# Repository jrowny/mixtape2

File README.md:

# A PCB for my mixtape project

_NOTE:_ this revision has NOT been tested! I changed some things from the video including moving the encoderes to different GPIOs and fixing the microsd card. Please verify closely before ordering.

3D models here: https://makerworld.com/en/models/3335806-cassette-mixtape-mp3-player-2-0#profileId-3789001
Video here: https://youtu.be/otXrFBq0HWQ

## This project was sponsored by NextPCB

Get your first PCB order for $0.1 via NextPCB: https://www.nextpcb.com/?code=JonathanRowny
Build PCBA in days with fully automated assembly: https://www.nextpcb.com/rev0-pcb

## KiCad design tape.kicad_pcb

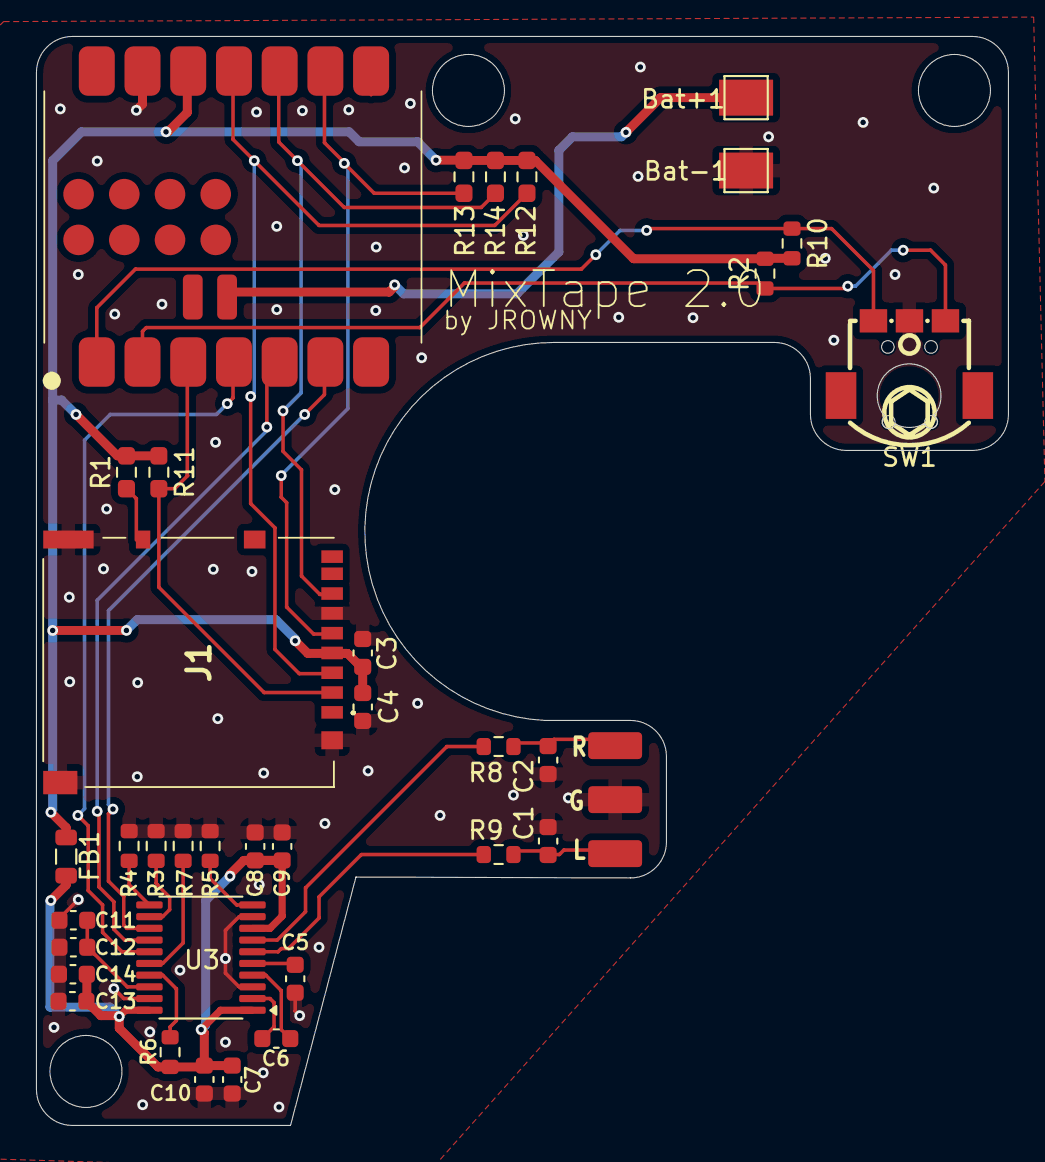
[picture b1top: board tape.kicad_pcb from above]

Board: 2 copper layers, 54.0 x 60.5 mm, 36 parts (0 on the bottom side), 26 nets.

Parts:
Bat+1: Bat+; TestPoint_Pad_2.0x2.0mm
Bat-1: Bat-; TestPoint_Pad_2.0x2.0mm
C1, C2: 2.2nF; C_0603_1608Metric
C3, C7, C9, C11, C14: 10uf; C_0603_1608Metric
C4, C8, C10, C12, C13: 0.1uF; C_0603_1608Metric
C5, C6: 2.2uF; C_0603_1608Metric
FB1: FerriteBead_Small; L_0805_2012Metric
J1: Micro_SD_Card_Det_Hirose_DM3AT; DM3ATSFPEJM5
R1, R11, R12, R13, R14: 10k; R_0603_1608Metric_Pad0.98x0.95mm_HandSolder
R2, R3, R4, R5, R6, R7, R10: 10k; R_0603_1608Metric
R8, R9: 470; R_0603_1608Metric
SW1: RotaryEncoder; EC05E1220401-JRmoded
U1: XIAO-ESP32-S3-SMD; XIAO-ESP32S3-SMD
U2: audio_out
U3: PCM5102A; TSSOP-20_4.4x6.5mm_P0.65mm

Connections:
/3v3: C3.2, C4.2, FB1.1, J1.4 (VDD), R1.1, R2.2, R10.2, R11.1, R12.1, R13.1, R14.1, U1.12 (3V3)
/3v3f: C7.1, C8.1, C9.1, C10.1, C13.1, C14.2, FB1.2, R6.2, U3.1 (CPVDD), U3.8 (AVDD), U3.20 (DVDD)
/BAT: Bat+1.1 (1_1), U1.15 (BAT)
/ENC_A: R2.1, SW1.A, U1.2 (GPIO2_A1_D1)
/ENC_B: R10.1, SW1.B, U1.1 (GPIO1_A0_D0)
/I2S_BCLK: U1.6 (GPIO6_A5_D5_SCL), U3.13 (BCK)
/I2S_DATA: U1.5 (GPIO5_A4_D4_SDA), U3.14 (DIN)
/I2S_LRC: U1.4 (GPIO4_A3_D3), U3.15 (LRCK)
/LDOO: C11.2, C12.1, U3.18 (LDOO)
/OUT_L: C1.2, R9.1, U2.1 (audio_left)
/OUT_R: C2.1, R8.1, U2.3 (audio_right)
/SD_CS: J1.2 (DAT3/CD), R11.2, U1.3 (GPIO3_A2_D2)
/SPI_MISO: J1.7 (DAT0), R14.2, U1.10 (GPIO8_A9_D9_MISO)
/SPI_MOSI: J1.3 (CMD), R12.2, U1.11 (GPIO9_A10_D10_MOSI)
/SPI_SCK: J1.5 (CLK), R13.2, U1.9 (GPIO7_A8_D8_SCK)
GND: Bat-1.1 (1_1), C1.1, C2.2, C3.1, C4.1, C5.2, C7.2, C8.2, C9.2, C10.2, C11.1, C12.2, C13.2, C14.1, J1.6 (VSS), R3.1, R4.1, R5.1, R7.1, SW1.C, U1.13 (GND), U1.16 (GND), U2.2 (gnd), U3.3 (CPGND), U3.9 (AGND), U3.19 (DGND)
unnamed: C6.2, U3.4 (CAPM)
unnamed: C6.1, U3.2 (CAPP)
unnamed: R5.2, U3.10 (DEMP)
unnamed: R4.2, U3.11 (FLT)
unnamed: R7.2, U3.16 (FMT)
unnamed: R9.2, U3.6 (OUTL)
unnamed: R8.2, U3.7 (OUTR)
unnamed: R3.2, U3.12 (SCK)
unnamed: C5.1, U3.5 (VNEG)
unnamed: R6.1, U3.17 (XSMT)
